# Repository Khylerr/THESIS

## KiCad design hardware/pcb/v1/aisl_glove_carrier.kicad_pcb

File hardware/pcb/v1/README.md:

# AISL-A glove carrier PCB v1

Generated 2026-11-18. **Not ordered, not built, not physically checked yet.** Design rules
pass (KiCad 9.0.7 DRC: 0 violations, 0 unconnected) and the board matches its schematic
(KiCad schematic parity: 0 issues), but a human still has to do the fit checks at the bottom
of this file before sending it to a fab.

Background, JP's decisions and the open questions are in `THESIS/HANDOFF.md` section 13.

## What it is

A 2-layer, all through-hole carrier board, **68 × 46.5 mm**, 1.6 mm FR4, hand-solderable.

- **U1** ESP32-DevKitC-32D plugs into two 1×19 female header sockets.
- **U2** MPU6050 module (GY-521) is soldered on its 1×8 header **underneath the DevKit**,
  between the two socket rows. Unplug the DevKit to reach it.
- **J1–J5** five 2-pin JST-XH sockets along one long edge, one per flex sensor, each with a
  10 k resistor (R1–R5) and a 100 nF capacitor (C1–C5) behind it.
- **J6** optional 1×2 pin header `5V IN` (DevKit `EXT_5V` pin + GND) for a future battery pack.
- **H1–H4** four M3 mounting holes (3.2 mm).

## Schematic

`aisl_glove_carrier.kicad_sch` is in the same KiCad project as the board, so opening
`aisl_glove_carrier.kicad_pro` in KiCad 9 gives both. Printable copy:
`schematic/aisl_glove_carrier_schematic.pdf`. It was redrawn on 2026-11-18 to match this
board and replaces the older drawing in `Glove kicad/glove/` (kept there untouched).

How to read it: each flex sensor sits between 3V3 and a node, and a 10 k resistor sits
between that node and GND. Bending the sensor changes its resistance, so the node voltage
changes, and the ESP32 measures that voltage. The 100 nF capacitor steadies the reading.
Boxes with a name (`FLEX1`, `I2C_SCL`, ...) are the same wire wherever the name appears.
Pins with an X are unused.

## Files

| Path | What |
|---|---|
| `build_carrier_pcb.py` | **The source of the board.** Edit this, not the `.kicad_pcb`. |
| `build_schematic.py` | **The source of the schematic.** Edit this, not the `.kicad_sch`. Also runs ERC and exports the PDF/SVG. |
| `aisl_ids.py` | Shared by both scripts so a symbol and its footprint carry the same ID. |
| `aisl_glove_carrier.kicad_sch` | The schematic, opens in KiCad 9. Regenerated (overwritten) by the script. |
| `schematic/` | Schematic as PDF, PNG and SVG. |
| `sym-lib-table`, `lib/aisl.kicad_sym` | Project symbol library (DevKit, MPU6050 module), generated by the script. |
| `lib/snapeda_original_symbols/` | Untouched SnapEDA symbols (copies of `Glove kicad/…`). |
| `check_schematic_vs_pcb.py` | Compares schematic and board pad by pad; writes `checks/schematic_vs_pcb.json`. |
| `compare_gerbers.py` | Compares two Gerber files as geometry (`compare_gerbers.py OLD NEW`), to prove a rebuild changed nothing. |
| `aisl_glove_carrier.kicad_pcb` / `.kicad_pro` | The board, opens in KiCad 9. Regenerated (overwritten) by the script. |
| `fp-lib-table`, `lib/aisl.pretty/` | Project footprint library, generated by the script. |
| `lib/snapeda_original.pretty/` | Untouched SnapEDA footprints (copies of `Glove kicad/…`). |
| `lib/3d/` | STEP models of the DevKit and the MPU6050 module (copies of `Glove kicad/…`). |
| `layout_summary.json` | Pad coordinates, hole positions and board size written by the script. |
| `fab/aisl_glove_carrier_gerbers.zip` | **Upload this to the fab** (7 Gerber layers + PTH and NPTH drill files). |
| `fab/gerbers/` | The same files unzipped, plus drill map PDFs. |
| `fab/BOM.csv` | Parts list. |
| `exports/aisl_glove_carrier_assembled.step` | 3D model of the populated board, for the enclosure. |
| `exports/aisl_glove_carrier_bare_board.step` | Board only. |
| `checks/drc.json`, `checks/drc_report.txt` | DRC results, including schematic parity. |
| `checks/erc.json`, `checks/erc_report.txt` | ERC (electrical rules check) of the schematic. |
| `checks/schematic_netlist.xml` | Netlist exported from the schematic; the board script reads it. |
| `checks/print_1to1_pin_fit_check.pdf` | Print at **100 % / actual size** for the paper fit check. |
| `renders/` | 01 top, 02 top with DevKit removed, 03 bottom, 04/05 perspective, 06 side. |

## Rebuild

Use KiCad's own Python (not the MediaPipe venv). From this folder:

```powershell
& "C:\Program Files\KiCad\9.0\bin\python.exe" build_schematic.py
& "C:\Program Files\KiCad\9.0\bin\python.exe" build_carrier_pcb.py
& "C:\Program Files\KiCad\9.0\bin\kicad-cli.exe" pcb drc --schematic-parity --format json --severity-all -o checks/drc.json aisl_glove_carrier.kicad_pcb
& "C:\Program Files\KiCad\9.0\bin\python.exe" check_schematic_vs_pcb.py
```

Schematic first: the board script reads the netlist it writes. All three checks must stay at
zero: ERC (`checks/erc_report.txt`), DRC with parity (`checks/drc.json`) and
`check_schematic_vs_pcb.py`. If you change the circuit, change it in **both** build scripts.

Then re-export Gerbers, drill, STEP and renders with `kicad-cli pcb export …` / `pcb render`
(exact commands are in `THESIS/HANDOFF.md` section 13.7). `AISL_VARIANT=no_devkit` makes a
second board file without the DevKit 3D model, used only for renders 02 and 05; delete it after.

## Netlist (read back from the generated board)

| Net | Pins |
|---|---|
| `+3V3` | DevKit `3V3` (J2-1), MPU `VCC`, pin 2 of J1–J5 |
| `GND` | DevKit `GND` ×3 (J2-14, J3-1, J3-7), MPU `GND` and `AD0`, R1–R5 pin 2, C1–C5 pin 2, J6 pin 2 |
| `FLEX1` | DevKit GPIO39 / `SENSOR_VN` (J2-4), J1 pin 1, R1, C1 |
| `FLEX2` | DevKit GPIO34 (J2-5), J2 pin 1, R2, C2 |
| `FLEX3` | DevKit GPIO35 (J2-6), J3 pin 1, R3, C3 |
| `FLEX4` | DevKit GPIO32 (J2-7), J4 pin 1, R4, C4 |
| `FLEX5` | DevKit GPIO33 (J2-8), J5 pin 1, R5, C5 |
| `I2C_SCL` | DevKit GPIO22 (J3-3), MPU `SCL` |
| `I2C_SDA` | DevKit GPIO21 (J3-6), MPU `SDA` |
| `+5V_EXT` | DevKit `EXT_5V` (J2-19), J6 pin 1 |

FLEX1…FLEX5 follow the firmware order `FLEX_PINS[5] = {39, 34, 35, 32, 33}`, so **no firmware
change is needed**. Which finger is flex1 is whatever the glove wiring is today; keep it.

Differences from the old KiCad 10 schematic in `Glove kicad/glove/` (out of date, replaced by
the schematic in this folder): filter caps go to **GND** instead of 3V3, flex sensors are
connectors J1–J5, J6 is new, and the references are renumbered (old R2/R4/R6/R8/R10 = 10 k,
here R1–R5).

The 29 unused pads (26 on the DevKit, `INT`, `XCL`, `XDA` on the MPU) each sit on their own
one-pad net named `unconnected-(...)`. That is KiCad's way of saying "deliberately not
connected" and adds no copper.

## Geometry (mm)

Coordinates are relative to the centre of the DevKit footprint, +X toward the USB end, +Y
toward the flex-connector edge. On the KiCad sheet add (100, 80).

| Item | Value |
|---|---|
| Outline | X −33 … +35, Y −15.2 … +31.3 (68 × 46.5), 2.5 mm corner radius |
| Mounting holes (3.2 mm) | (−29.5, −11.5), (31.5, −11.5), (−29.5, 27.8), (31.5, 27.8): **61 × 39.3 mm** pattern |
| DevKit socket rows | Y = ±12.7 (25.4 mm apart), pins X = −19.76 … +25.96, 2.54 pitch |
| DevKit body overhang | X −27.4 … +27.5; antenna at −X, USB at +X |
| MPU6050 module centre | (−5.79, 0); header row at Y = +6.33, `VCC` at X = −14.68 … `INT` at X = +3.10 |
| JST pins | Y = 27.1; cells centred X = −19, −9, 1, 11, 21 (J1 … J5) |
| 5V header J6 | 5V (30.5, 15.0), GND (30.5, 17.54) |
| Heights above the carrier top (nominal) | JST 7.0; socket top 8.5; MPU parts ≈ 5.5, its header pins ≈ 8.6; DevKit PCB 11.0–12.6; tallest DevKit part ≈ 16 |
| Below the carrier | solder joints / trimmed leads ≈ 2 |

Tracks: 0.4 mm signals, 0.6 mm 3V3, 0.8 mm 5 V, no vias. Ground pour on both sides, pulled back
under the ESP32 antenna and round every non-plated hole.

## Must check before ordering

1. **Print `checks/print_1to1_pin_fit_check.pdf` at 100 %** and lay the real parts on it:
   - DevKit: 19 pins per side and rows 25.4 mm apart. (A 30-pin "DOIT" board will not fit.)
   - MPU6050 module: with the header on the printed row, the label order must read
     `VCC GND SCL SDA XDA XCL AD0 INT` from the antenna side to the USB side, **and the
     module body must point toward the top socket row**, not toward the flex connectors.
     The pin order comes from an unverified SnapEDA footprint. If the body points the other
     way it will hit the bottom socket row and the footprint has to be flipped in the script.
2. Height: the MPU module has to fit under the DevKit (≈ 11 mm free). Fine with a standard
   2.54 mm header, **not** if the module sits on a tall socket.
3. Flex sensor leads need JST XH plugs (housing XHP-2). Direction does not matter.
4. Decide with Paulo whether the caps to GND change is acceptable (HANDOFF 13.2 item 1).
5. Have someone open the board in KiCad and look it over.

## Known limits

- Schematic and board are two generated files that are checked against each other, not one
  drawn from the other. Do not use KiCad's "Update PCB from Schematic" to change the circuit:
  the next script run overwrites both files. Change the two scripts instead.
- J6 feeds the DevKit's 5V pin. Power the board from USB **or** from J6, not both at once.
- 3D model heights are nominal (DevKit model placed for an 8.5 mm socket + 2.54 mm header).
- The IMU sits under the ESP32 and will warm up a little with it. Zero it (CAL) after the
  board has been on for a few minutes.
- Use nylon screws at H1/H3 if possible: they are next to the antenna.

## Ordering from Aivon (aivon.com), chosen by JP 2026-11-18

Checked on their site on 2026-11-18. The **only file they need for a bare board** is
`fab/aisl_glove_carrier_gerbers.zip` (they accept zip/rar under 10 MB; ours is about 80 KB).
Do not put the `.kicad_pcb` in the same zip. No BOM or pick-and-place file is needed, because
we solder the parts ourselves (those are only for their assembly service).

On their "PCB Quote" page (`online-pcb-quote-new.html`) upload the zip, then set:

| Field | Value |
|---|---|
| Material Type | FR-4 |
| Layers | 2 |
| Dimensions | 46.5 × 68 mm |
| Board Type | Single PCB |
| Quantity | 5 (the minimum) |
| Thickness | 1.6 |
| Outer Copper | 1oz |
| Solder Mask / Silkscreen | any / white (silkscreen must contrast with the mask) |
| Min Spacing | 6/6mil↑ (our smallest gap is 0.25 mm ≈ 10 mil, tracks ≥ 0.4 mm) |
| Min Hole Size | 0.3mm↑ (our smallest hole is 0.8 mm) |
| Via Process | leave default (the board has no vias) |
| Surface Finish | HASL Lead Free (or HASL with Lead: cheaper and easier to hand-solder) |
| Project File Confirm | Yes (they send their production file for you to check before making it) |

Their review will show 78 plated holes and 6 non-plated 3.2 mm holes; that is correct.
Prices on the site exclude customs duty and VAT. Nobody has uploaded or ordered anything yet.

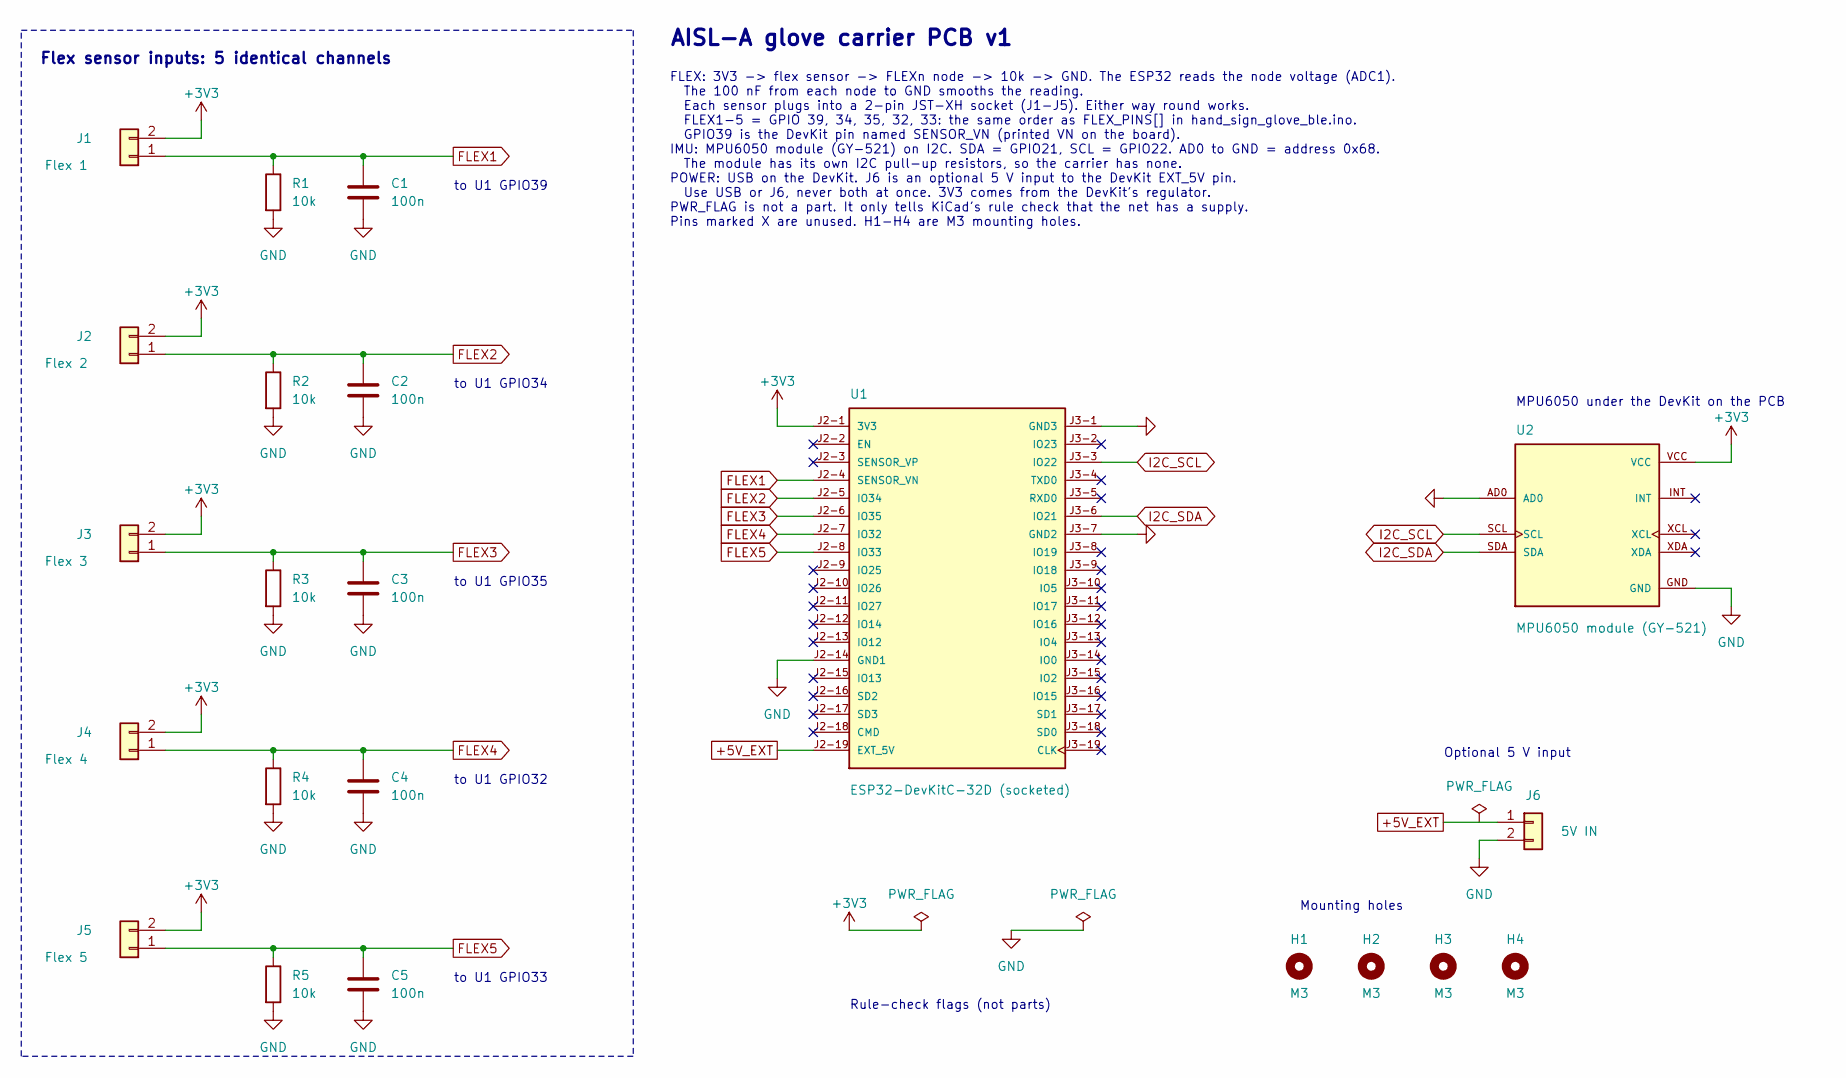
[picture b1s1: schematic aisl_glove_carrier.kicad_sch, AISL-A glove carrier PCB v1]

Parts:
C1, C2, C3, C4, C5: 100n; C_Disc_D5.0mm_W2.5mm_P5.00mm
H1, H2, H3, H4: M3; MountingHole_3.2mm_M3
J1: Flex 1; JST_XH_B2B-XH-A_1x02_P2.50mm_Vertical
J2: Flex 2; JST_XH_B2B-XH-A_1x02_P2.50mm_Vertical
J3: Flex 3; JST_XH_B2B-XH-A_1x02_P2.50mm_Vertical
J4: Flex 4; JST_XH_B2B-XH-A_1x02_P2.50mm_Vertical
J5: Flex 5; JST_XH_B2B-XH-A_1x02_P2.50mm_Vertical
J6: 5V IN; PinHeader_1x02_P2.54mm_Vertical
R1, R2, R3, R4, R5: 10k; R_Axial_DIN0207_L6.3mm_D2.5mm_P7.62mm_Horizontal
U1: ESP32-DevKitC-32D (socketed); ESP32-DevKitC-32D_socketed
U2: MPU6050 module (GY-521); MPU6050_GY-521_module

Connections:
+3V3: J1.2, J2.2, J3.2, J4.2, J5.2, U1.J2-1 (3V3), U2.VCC
+5V_EXT: J6.1, U1.J2-19 (EXT_5V)
FLEX1: C1.1, J1.1, R1.1, U1.J2-4 (SENSOR_VN)
FLEX2: C2.1, J2.1, R2.1, U1.J2-5 (IO34)
FLEX3: C3.1, J3.1, R3.1, U1.J2-6 (IO35)
FLEX4: C4.1, J4.1, R4.1, U1.J2-7 (IO32)
FLEX5: C5.1, J5.1, R5.1, U1.J2-8 (IO33)
GND: C1.2, C2.2, C3.2, C4.2, C5.2, J6.2, R1.2, R2.2, R3.2, R4.2, R5.2, U1.J2-14 (GND1), U1.J3-1 (GND3), U1.J3-7 (GND2), U2.AD0, U2.GND
I2C_SCL: U1.J3-3 (IO22), U2.SCL
I2C_SDA: U1.J3-6 (IO21), U2.SDA

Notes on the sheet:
to U1 GPIO39
to U1 GPIO34
to U1 GPIO35
to U1 GPIO32
to U1 GPIO33
Flex sensor inputs: 5 identical channels
AISL-A glove carrier PCB v1
FLEX: 3V3 -> flex sensor -> FLEXn node -> 10k -> GND. The ESP32 reads the node voltage (ADC1). The 100 nF from each node to GND smooths the reading. Each sensor plugs into a 2-pin JST-XH socket (J1-J5). Either way round works. FLEX1-5 = GPIO 39, 34, 35, 32, 33: the same order as FLEX_PINS[] in hand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
MPU6050 under the DevKit on the PCB
Optional 5 V input
Rule-check flags (not parts)
Mounting holes

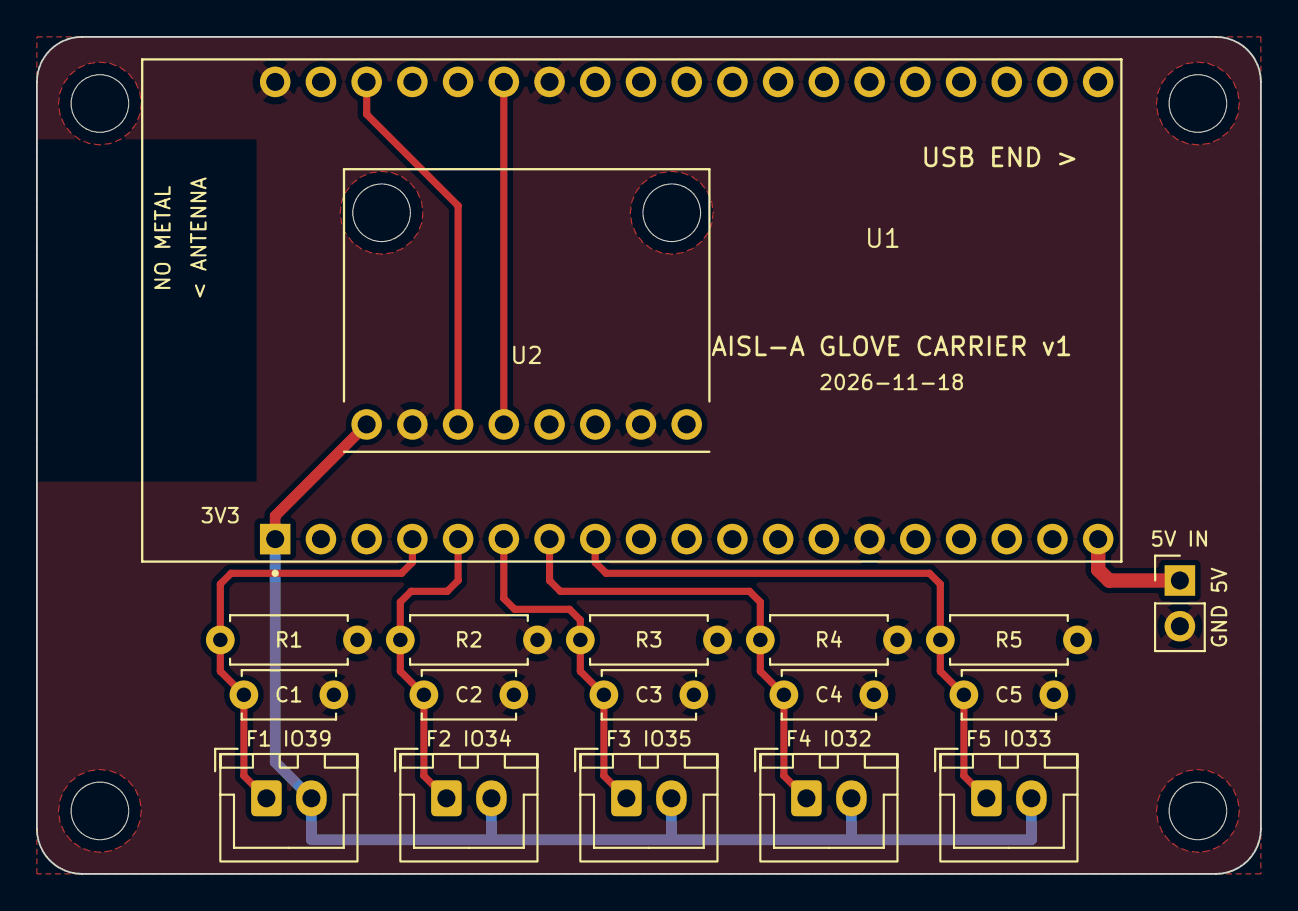
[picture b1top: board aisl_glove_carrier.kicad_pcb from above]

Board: 2 copper layers, 68.0 x 46.5 mm, 22 parts (0 on the bottom side), 10 nets.

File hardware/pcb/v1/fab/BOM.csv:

Ref,Qty,Value,Part / footprint,Notes
U1 sockets,2,1x19 female header 2.54 mm,PinSocket_1x19_P2.54mm_Vertical (8.5 mm tall),ESP32-DevKitC-32D (38 pin) plugs in. Have it already.
U2,1,MPU6050 module (GY-521),1x8 male header 2.54 mm soldered to carrier,Existing module. Sits UNDER the DevKit.
R1-R5,5,10k 1/4 W 1% axial,R_Axial_DIN0207 7.62 mm pitch,Divider bottom resistor (ADC node to GND)
C1-C5,5,100 nF ceramic,C_Disc 5.0 mm pitch (2.5 mm parts fit with bent leads),ADC node to GND
J1-J5,5,JST XH 2-pin vertical header B2B-XH-A,2.5 mm pitch,One per flex sensor
(cable side),5,JST XHP-2 housing + 10 SXH-001T-P0.6 crimps,or pre-crimped XH 2-pin leads,Solder to the flex sensor leads
J6,1,1x2 male pin header 2.54 mm,PinHeader_1x02_P2.54mm_Vertical,Optional 5V IN. Leave empty if unused.
H1-H4,4,M3 screw + standoff,3.2 mm holes,Nylon preferred at the antenna end (H1 and H3)
PCB,1,68 x 46.5 mm 2-layer 1.6 mm FR4,HASL any colour,Gerbers in fab/aisl_glove_carrier_gerbers.zip
